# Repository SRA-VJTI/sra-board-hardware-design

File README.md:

<!-- PROJECT LOGO -->

[![Stargazers][stars-shield]][stars-url]
[![Forks][forks-shield]][forks-url]
[![Issues][issues-shield]][issues-url]
[![License][license-shield]][license-url]

<br/>

<p align="center">

  <h3 align="center">SRA Development Board</h3>
  <p align="center">
    ESP32-based Development Board
    <br />
    <a href="./sra_dev_board_2026">KiCAD</a>
    ·
    <a href="./gerber_sra_dev_board">Gerber</a>
    ·
    <a href="./documentation/images/board_images/front.png">Images</a>
    ·
    <a href="./3d_models/sra_board_model/sra_dev_board_2026.step">3D Model</a>
  </p>

# SRA Board 2026

The SRA board is a development board based on ESP32 with on-board peripherals like a programmable LED matrix, switches, sensor ports for Line Sensor Array and MPU-6050, protection circuit for over-current and reverse voltage, and motor drivers.

## Table of Contents

- [SRA Board 2026](#sra-board-2026)
  - [Table of Contents](#table-of-contents)
  - [Board Images](#board-images)
  - [About the Project](#about-the-project)
  - [Getting Started with a Development Board](#getting-started-with-a-development-board)
  - [Notable problems in the current SRA Board](#notable-problems-in-the-current-sra-board)
  - [Improvements Suggested for Future Iterations](#improvements-suggested-for-future-iterations)
  - [Potential Future Enhancements](#potential-future-enhancements)
  - [3D Models](#3d-models)
  - [Milestones](#milestones)
  - [Contributors](#contributors)
  - [Acknowledgements and Resources](#acknowledgements-and-resources)
  - [License](#license)

## Board Images

- **Frontside**

- **Backside**

## About the Project

- This development board is used for the [Wall-E](https://github.com/SRA-VJTI/Wall-E) and [MARIO](https://github.com/SRA-VJTI/MARIO) workshops conducted by [SRA](https://github.com/SRA-VJTI).
- Designed using KiCAD. The schematic and board files are [here](./sra_dev_board_2026).
- Resources for [previous work](https://github.com/SRA-VJTI/sra-board-hardware-design/tree/v2.5). For more details of the SRA board 2024, checkout this [link](https://github.com/SRA-VJTI/sra-board-hardware-design/releases/tag/v2.4).
- The SRA board 2023 images can be found [here](https://github.com/SRA-VJTI/sra-board-hardware-design/tree/v2.3/documentation/images).
- Older versions of the board and miscellaneous designs can be found [here](https://github.com/SRA-VJTI/PCB-Schematics-and-Layouts).

## Getting Started with a Development Board

In general, every development board has the following basic features:

- ### Power Supply Unit
  - Microcontrollers (MCUs) usually run on 3.3V or 5V logic supply voltage while input to a development board is normally 12V for motor and driving/controlling peripheral devices.
  - So, in order to have a single input source, a _power_ section which inter converts this 12V to standard levels like 5V & 3.3V for MCU and sensors is present.This is achieved using a step-down [buck regulator](https://www.youtube.com/watch?v=m8rK9gU30v4).
  - Buck Regulator IC [MP1584](./datasheets/MP1584_buck.pdf) is used in the current SRA Board 2026 for stepping down the voltage from 12V to 5V DC. This 5V is further regulated to 3.3V using LDO IC [AMS1117-3.3](./datasheets/ams1117_ldo.pdf). The MP1584 is a more compact and efficient alternative compared to the previous LM2576-S.
  - The previous edition of the SRA board (2025) used the [LM2576-S-5](./datasheets/lm2576_buck_regulator.pdf) buck regulator, while earlier editions used the LM7805 linear voltage regulator for stepping down from 12V to 5V.
  - The older editions of the SRA board used the LD33 linear voltage regulator for converting 5V to 3.3V at the sensor port.

- ### Motor Driver
  - Motors usually run on 12V and MCU output is generally 5V/3.3V. So, an external motor driver circuitry is required to control motors according to the MCU input.
  - The current and previous editions of SRA board use the [TB6612FNG](./datasheets/TB6612FNG_motor_driver.pdf) Motor Driver, which is a MOS-based H-Bridge motor driver.
  - The older editions of SRA Board used the L298N IC for motor-control, which is a BJT-based H-Bridge motor driver.

- ### Sensor Port
  - According to the external sensor types, usually development boards have onboard sensor ports where the sensors can be connected easily. [LSA - Line Sensor Array]() and [MPU- Motion Processing Unit]() have on-board connection ports.
  - The current edition uses easily available and efficient [JST XH connectors](https://en.wikipedia.org/wiki/JST_connector).
  - Previous versions used bulky [FRC connectors](<https://www.sunrom.com/c/frc-idc-flat-cable-box-header#:~:text=FRC%20(Flat%20Ribon%20Cable)%20are,from%206%20to%2064%20pins.>)

- ### Protection against [Reverse Voltage](https://www.google.com/url?sa=t&rct=j&q=&esrc=s&source=web&cd=&cad=rja&uact=8&ved=2ahUKEwjc8aaX1c3rAhXXXSsKHXphBgQQFjABegQICxAD&url=https%3A%2F%2Fwww.ti.com%2Flit%2Fpdf%2Fslva139&usg=AOvVaw0Qbub75JJ986MzLv6FYWKE)
  - The SRA Boards use diodes for reverse voltage protection in the power-line.
  - 12V Motor line and power regulated line have been separated with [SS34](./datasheets/ss34_3A_schottky_diode.pdf) and [SS54](./datasheets/ss24_2A_schottky_diode.pdf) schottky diodes respectively.

- ### Protection against [Over Current](https://www.baypower.com/blog/what-is-overcurrent-protection/#:~:text=Overcurrent%20protection%20is%20the%20method,of%20a%20piece%20of%20equipment.)
  - Earlier, for the overcurrent protection of MCU and motor driver circuit, bulky glass fuses of 300mA and 3A were used respectively. After breakdown, they used to be replaced.
  - In the recent versions of the board, these were replaced with compact, PTC Resettable Fuses.
  - On 12V line - [RXEF160](./datasheets/RUEF160_3,2A_trip_ptc_fuse.pdf) : 1.6A hold current; 3.2A trip current Fuse was used.
  - On 5V line - [RXEF160](./datasheets/RXEF050_1A_trip_ptc_fuse.pdf) : 0.5A hold current; 1A trip current Fuse was used.
- ### Programmable Switches and LEDs
  - Every development board should have some programmable switches and LEDs for testing, control and debugging purposes.
  - The current SRA Board 2026 features a 6x5 LED matrix (30 LEDs total) controlled via shift registers, which provides enhanced debugging capabilities and expressive visual feedback while reducing GPIO usage compared to discrete LEDs.
  - The previous edition (2025) had an array of 8 programmable discrete LEDs and switches.
  - The earlier editions had fewer programmable switches and LEDs for testing and control purposes.

- ### Power Switch
  - All versions have a power switch for the motor driver, using which power supply to the motor driver can be toggled. Similarly, there was a switch for the ESP32 MCU.

> Now that we covered basics of development boards, let us talk about the changes made in the new design.

## Changes IN SRA Board Over the years from 2024-2026

|            Feature            |           SRA Board 2024           |           SRA Board 2025           |            SRA Board 2026            |
| :---------------------------: | :--------------------------------: | :--------------------------------: | :----------------------------------: |
|           12V to 5V           |      LM2576-S Buck Converter       |      LM2576-S Buck Converter       |        MP1584 Buck Converter         |
|  Reverse Voltage Protection   |               Diodes               |               Diodes               |                Diodes                |
|   Line Sensing Arrays (LSA)   |             IR Sensors             |             IR Sensors             |              IR Sensors              |
|     Number of LSA Sensors     |                 5                  |                 5                  |                  5                   |
|         Motor Driver          |             TB6612FNG              |             TB6612FNG              |              TB6612FNG               |
|     Stepper Motor Driver      |                 -                  |                 -                  |                  -                   |
|   No. of DC Motor Channels    |                 2                  |                 2                  |                  2                   |
| No. of Stepper Motor Channels |                 0                  |                 0                  |                  0                   |
|        No. of Switches        |                 2                  |                 2                  |                  2                   |
|          No. of LEDs          |                 8                  |                 8                  | 6x5 LED Matrix (via Shift Registers) |
|    Over Current Protection    |        PTC Resettable Fuses        |        PTC Resettable Fuses        |         PTC Resettable Fuses         |
|    Sensor Port Connectors     |           JST Connectors           |           JST Connectors           |            JST Connectors            |
| Component Type and Board Size | SMD(Surface Mount Device), Smaller | SMD(Surface Mount Device), Smaller |  SMD(Surface Mount Device), Smaller  |
|         ESP32 Module          |           Not Integrated           |    Mounted and Soldered to PCB     |     Mounted and Soldered to PCB      |
|         Flashing Port         |             Micro USB              |               Type-C               |                Type-C                |

- ### **Compatiblity of SRA Board with Battery [3- 3.3V 2500mAh Batteries](https://robu.in/product/bak-nmc-18650-2500mah-8c-lithium-ion-battery/?gad_source=1&gclid=Cj0KCQjw6PGxBhCVARIsAIumnWb20iyJUEXE8V6eAfSambP35PfBsSFKje-ALjyNniqGYCW_kz3IbcQaAoeGEALw_wcB)**
  - The SRA Board is compatible with **3-cell (3S) Lithium-ion battery packs** which use an external **[BMS (Battery Management System)](https://robu.in/product/3s-10a-12v-18650-lithium-battery-charger-board-protection-module/)**.
  - The BMS helps maintain safe operating voltages and disconnects the battery when the voltage drops below a safe limit.
  - It also ensures balanced charging and discharging of the three cells, improving the overall health and lifetime of the battery pack.

- ### **7805 (5V linear regulator) to [LM2576/96 Buck Convertor](https://www.youtube.com/watch?v=m8rK9gU30v4)**
  - The higher efficiency, output current capability and reliability of LM2576/96 were the primary reasons for this change.
  - The efficiency of LM2576 can reach up to **~92%**, which is significantly better than the 7805 linear regulator.
  - The LM2576 can provide currents up to **3A**, allowing peripherals such as the MARIO workshop manipulator to be powered using the onboard regulator.

- ### **LD33 (3.3V) to [AMS1117](http://www.advanced-monolithic.com/pdf/ams1117.pdf)**:
  - Older editions used the **LD33 IC** to step down from 5V to 3.3V.
  - This was later replaced with the **AMS1117-3.3 LDO**, which is more compact and widely used for stable 3.3V regulation.
  - (_AMS1117 is also used on the ESP32-DevKitC V4 module._)

- ### **Reverse voltage protection: Diodes to P-MOSFET**
  - Diodes placed in series with the power line introduce voltage drop and power loss compared to a **P-MOSFET based protection circuit**.
  - Due to the higher current requirements of the motors, managing diode size and current rating became difficult.
  - Therefore, earlier versions used a **P-MOSFET based reverse polarity protection circuit**, which is more efficient and can handle higher currents.
  - In the current edition, **SMD Schottky diodes** are used, making size and rating less of an issue.

- ### **Component Type and Board Size**:
  - In the previous editions, THT/PTH (Through-Hole) components were used, which occupied more board area and increased in size with higher power ratings.
  - In the current edition, the design adopts a more compact SMD-based layout. The LM2576 buck converter has been replaced with the smaller MP1584 regulator, and the discrete LED array has been replaced with a 6×5 LED matrix driven using shift registers.
  - Current Board Dimensions: **90mm x 90mm**

- ### **L298N vs [TB6612FNG](https://dronebotworkshop.com/tb6612fng-h-bridge/)**
  - L298N is a BJT-based H-bridge motor driver but it is less efficient as compared to the new MOS-based TB6612FNG.
  - The detailed comparison is shown below. As you can see the efficiency of TB6612FNG can reach up to 91-95% which is significantly higher than the 40-70% efficiency of L298N.
  - The only drawback of TB6612FNG is the less continuous current which is equal to 1.2A.

- ### **LED System**

  - Earlier versions of the board used a set of discrete programmable LEDs for debugging and status indication. In the SRA Board 2026, this has been replaced with a **6×5 LED matrix driven using shift registers**.  
  - This significantly reduces GPIO usage while allowing more flexible visual debugging and status indication patterns.

## Notable problems in the current SRA Board

- ### **Buck Converter Stability Issue (MP1584)**
  - The SRA Board 2026 uses the **MP1584 buck converter** to step down 12V to 5V.
  - While the device allowed a significant reduction in the power section size compared to LM2576, irregular behaviour was observed under **higher load conditions**.
  - During heavy load scenarios involving motors and other peripherals, the **5V rail occasionally showed instability**, which may affect the overall system reliability.

- ### **USB Type-C Connector Mechanical Strength Issue**
  - The board currently uses a **16-pin USB Type-C connector** for programming and power.
  - In practical usage, the connector was found to be **mechanically weak**, and in some cases it could loosen or detach from the PCB after repeated cable insertion or mechanical stress.

- ### **Power Switch Issue**
  - There are two dpdt power toggle switch used on board. One to toggle the supply of 12v to the whole board and one to toggle the supply of 5v to the logic circuit.
  - Instead it should have been toggling 12v supply to the motors and toggling 12v supply to the whole board.

## Improvements Suggested for Future Iterations

Based on the current design of the SRA Board 2026, the following improvements are recommended for future iterations:

- **Replace MP1584 with TPS562202**: The TPS562202 offers improved reliability and enhanced long-term robustness compared to the current MP1584 buck converter. This component provides better thermal performance and more stable regulation across varying load conditions.

- **Upgrade to USB-C 6P Connector**: Replace the current Type-C connector with a robust USB-C 6P connector configuration. This simplifies soldering procedures, improves mechanical strength, and enhances durability during repeated connection cycles.

- **Add Unconnected UART Solder Pads (RX, TX)**: Incorporate unconnected solder pads for UART receive and transmit lines on the PCB. This allows the board to optionally function as a USB-to-TTL interface, extending its utility beyond standalone development applications.

## Potential Future Enhancements

The following experimental features and enhancements are being considered for future versions of the SRA Board but are not yet integrated into the 2026 iteration:

- **Onboard IMU Integration**: Direct integration of an Inertial Measurement Unit (IMU) for advanced motion sensing applications, eliminating the need for external MPU6050 connections.

- **Camera FFC/FPC Connector**: Addition of a Flat Flex Cable (FFC) or Flexible Printed Circuit (FPC) connector to support camera modules, enabling vision-based robotics projects and computer vision applications.

- **Integrated Motor Driver**: Direct onboarding of motor driver circuits instead of requiring external TB6612FNG modules, reducing component count and improving form factor.

- **CH340 to CP2102 Upgrade**: Replacing the CH340 USB-to-UART bridge with CP2102 for improved reliability, driver support across multiple operating systems, and better stability in industrial environments.

These enhancements represent opportunities for evolution of the platform and will be explored as future iterations of the board are developed.

## 3D Models

1. The complete 3D model (.step) file of [SRA Board 2026](./3d_models/sra_board_model/sra_dev_board_2026.step)
2. The 3D models of motor driver, LEDs, ESP32 etc.: [3d models of other components](./3d_models/)

<!-- Milestone -->

## Milestones

- [x] Designing of the prototype board
- [x] Modular testing of the circuit
- [x] Testing of prototype board
- [x] Final version
- [x] Making the board Battery Compatible
- [x] Onboard ESP32 Module

<!-- CONTRIBUTORS -->

## Contributors

- [Vishal Mutha](https://github.com/Vishal-Mutha): _Designer_
- [Atharva Atre](https://github.com/AtharvaAtre): _Mentor_
<!-- ACKNOWLEDGEMENTS AND REFERENCES -->

## Acknowledgements and Resources

- Previous Edition: [SRA Board 2025](https://github.com/SRA-VJTI/sra-board-hardware-design/releases/tag/v2.5)
- [KiCAD Tutorials](https://www.youtube.com/playlist?list=PL3bNyZYHcRSUhUXUt51W6nKvxx2ORvUQB)
- [README Template](https://github.com/roshanlam/ReadMeTemplate) by [roshanlam](https://github.com/roshanlam)

## License

- Distributed under the [MIT License](https://github.com/SRA-VJTI/sraboard-hardware-design/blob/master/LICENSE).

[forks-shield]: https://img.shields.io/github/forks/SRA-VJTI/sra-board-hardware-design
[forks-url]: https://github.com/SRA-VJTI/sra-board-hardware-design/network/members
[stars-shield]: https://img.shields.io/github/stars/SRA-VJTI/sra-board-hardware-design
[stars-url]: https://github.com/SRA-VJTI/sra-board-hardware-design/stargazers
[issues-shield]: https://img.shields.io/github/issues/SRA-VJTI/sra-board-hardware-design
[issues-url]: https://github.com/SRA-VJTI/sra-board-hardware-design/issues
[license-shield]: https://img.shields.io/github/license/SRA-VJTI/sra-board-hardware-design
[license-url]: https://github.com/SRA-VJTI/sra-board-hardware-design/blob/master/LICENSE

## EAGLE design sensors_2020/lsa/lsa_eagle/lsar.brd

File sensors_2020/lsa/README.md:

## LSA - Light Sensor Array

### Table of Contents
* [Overview](#overview)
* [Features](#features)
* [Components of LSA](#components-of-lsa)
* [Function of Components](#function-of-components)
	* [LED](#function-of-components)
	* [PhotoDiode](#function-of-components)
	* [IC LM324](#function-of-components)
	* [Resistors](#function-of-components)
* [Working Principle](#working-principle)
* [Appplications](#applications)
* [Scope of Improvement](#scope-of-improvement)
* [Description of Functions Used](#description-of-functions-used)

### Overview 
- The Light Sensor Array(LSA) is used to detect the white/black lined surface and it sends this data to the microcontroller ESP-32. Analyzing and processing the data received by the microcontroller ESP-32, the purpose of line following is achieved.

- Physical PCB

- PCB Model

###Features
* Components used are readily available.
* Easy connections for output signals.
* Compact enough to fit into any project.
* Distinguished trace widths for Signal and Power Routes.

### Components of LSA
| Component   | Description   | Quantity |
| ----------- | ------------- | -------- |
| LED         | Emits light   |  4       |
| PhotoDiode  | Absorbs light |  4       |
| IC LM324    | Op.Amp. IC    |  1       |  
| Resistors   | Limit Current |  8       |
|JST Connector | Connect PCB with other circuits|1|

### Function of Components
- LED
	- LSA consists of Four LED and PhotoDiode Pairs. The specific LED's emit white light which is incident on the surface and some of it is absorbed by the surface. The voltage source For the LEDs to glow is VCC.

- PhotoDiode
	- Based upon the reflectivity coefficient of the surface( generally less than 1), the remaining light reflected from the surface is captured by the Photodiodes. LEDs and complimentary photodiodes are used to efficiently detect the surface (white/black line) as the environment also contains unwanted light for the LSA sensor. The amount of light received is directly proportional to the current generated by it. More the light, more the current, more the reading.
 
- IC LM324 
	- This is a Quad(4) OP.Amp. IC. Op.Amp i.e Operation Amplifiers amplify the current with constant volatge. Since the current reading from photo diodes is significantly small and difficult to compare, it needs to be amplified. The 4 amplified outputs serve as raw readings of LSA.

- Resistors
	- Now to limit the current and thus to protect the LEDs, PhotoDiodes current limiting resistors are used.

### Working Principle
- LSA works on the principle of reflectivity of light for different types of surfaces.
	- Black Surface -> HIGH absorptivity -> LESS reflectivity
	- White Surface -> LOW absorptivity -> HIGH reflectivity
- Demonstration

### Applications
* Obstacle detection on a clear path.
* Line Following.
* Distinguish Colours on a path.

### Scope of Improvement
- LSA sometimes provides slightly inaccurate readings due to external light and conditions due to non uniformity of the colour of the path. Therefore, LSA has low accuracy. Hence LSA should be kept close to the ground.
- As of now only white and black surfaces are being mapped. Given accurate sensors and proper mapping we can map LSA for any range of RGB colours.

### Description of Functions Used
* ```c
    esp_err_t enable_line_sensor(int mode)	
    ```
    **Description** : Enables and Configures the adc(Analog to Digital Converter).	.

    **Parameters** :
    * `None` 

    **Returns** : esp_err_t returns ESP_OK if adc is initialised properly, else it returns ESP_ERR_INVALID_ARG
    
* ```c
    float bound(float val, float min, float max)	
    ```
    **Description** : Bounds the given val within the range [min, max].

    **Parameters** :
    * `val` : the value which needs to be bounded in the range [min, max].
    * `min` : the minimium limit value of the bounding range.
    * `max` : the maximum limit value of the bounding range.

    **Returns** : the bounded value of val within the bounding range.
    
* ```c
    float map(float val, float input_lower_limit, float input_higher_limit, float output_lower_limit, float output_higher_limit)	
    ```
    **Description** : Maps the range [input_lower_limit, input_higher_limit] to  the range [output_lower_limit, output_higher_limit].

    **Parameters** :
    * `val` : the value which needs to be mapped.
    * `input_lower_limit` : the minimium limit value of the input mapping range.
    * `input_lower_limit` : the maximum limit value of the input mapping range.
    * `output_lower_limit` : the minimium limit value of the output mapping range.
    * `output_lower_limit` : the maximum limit value of the output mapping range.
    
    **Returns** : the mapped value of val lying within the output mapping range.
    
* ```c 
    void vTaskDelay(const TickType_t xTicksToDelay)
  ```

  **Description** : Delay a task for a given number of ticks.The constant portTICK_PERIOD_MS can be used to calculate real time from the tick rate - with the     resolution of one tick period.

  **Parameters** : 
  * `xTicksToDelay` : The amount of time, in tick periods, that the calling task should block.

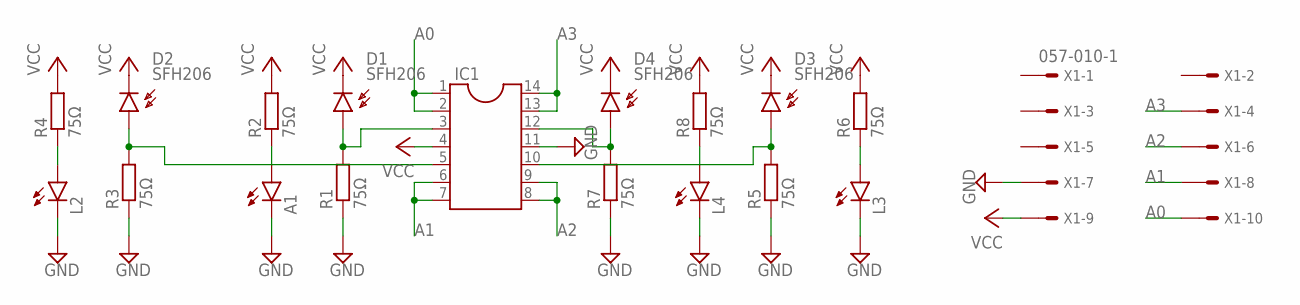
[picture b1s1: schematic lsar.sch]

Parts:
A1: LED3MM
D1, D2, D3, D4: SFH206
IC1: DIL14S; SOCKET-14
L2, L3, L4: LED3MM
R1, R2, R3, R4, R5, R6, R7, R8: 75Ω; 0207/10
X1: 057-010-1

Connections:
A0: IC1.1, IC1.2, X1.10
A1: IC1.6, IC1.7, X1.8
A2: IC1.8, IC1.9, X1.6
A3: IC1.13, IC1.14, X1.4
GND: A1.K (C), IC1.11, L2.K (C), L3.K (C), L4.K (C), R1.1, R3.1, R5.1, R7.1, X1.7
unnamed: A1.A, R2.1
unnamed: D1.A, IC1.3, R1.2
unnamed: L2.A, R4.1
unnamed: D2.A, IC1.5, R3.2
unnamed: L4.A, R8.1
unnamed: D4.A, IC1.12, R7.2
unnamed: L3.A, R6.1
NS7: D3.A, IC1.10, R5.2
VCC: D1.K (C), D2.K (C), D3.K (C), D4.K (C), IC1.4, R2.2, R4.2, R6.2, R8.2, X1.9

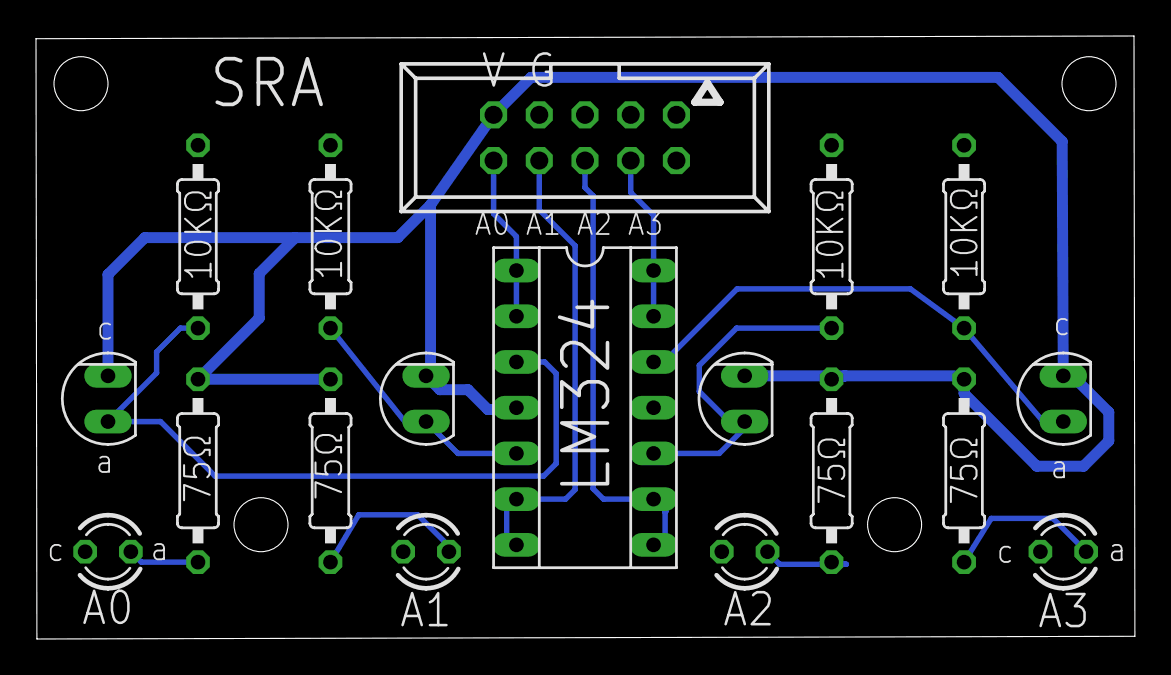
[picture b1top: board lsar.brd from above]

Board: 2 copper layers, 61.0 x 33.5 mm, 18 parts (0 on the bottom side), 14 nets.

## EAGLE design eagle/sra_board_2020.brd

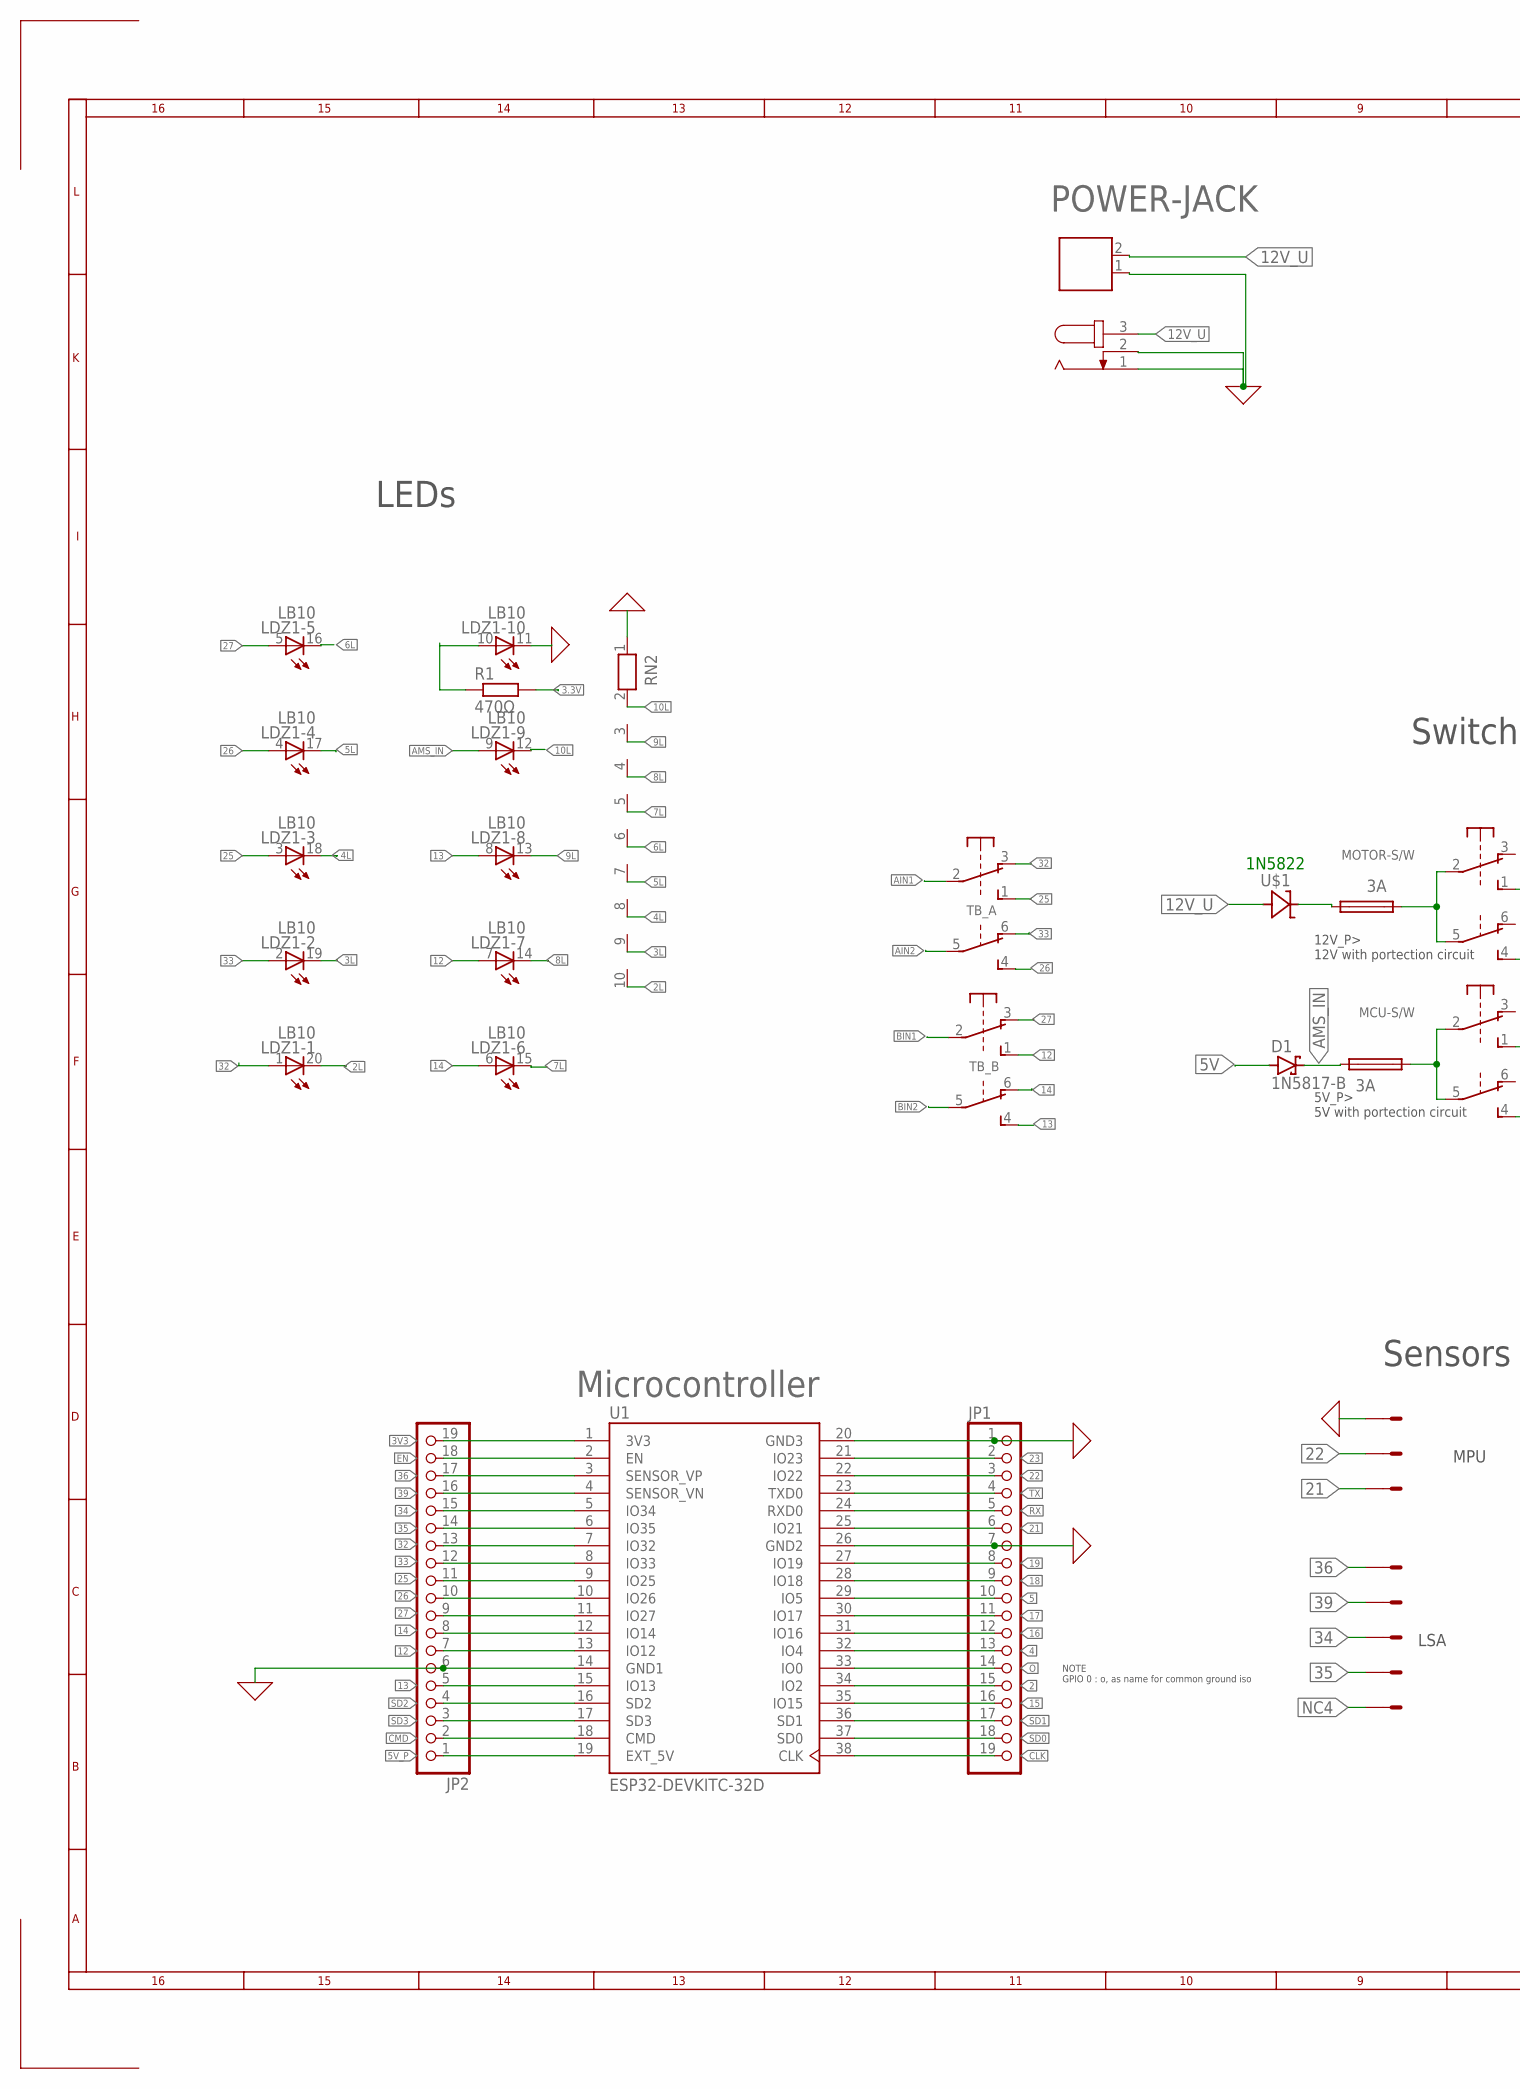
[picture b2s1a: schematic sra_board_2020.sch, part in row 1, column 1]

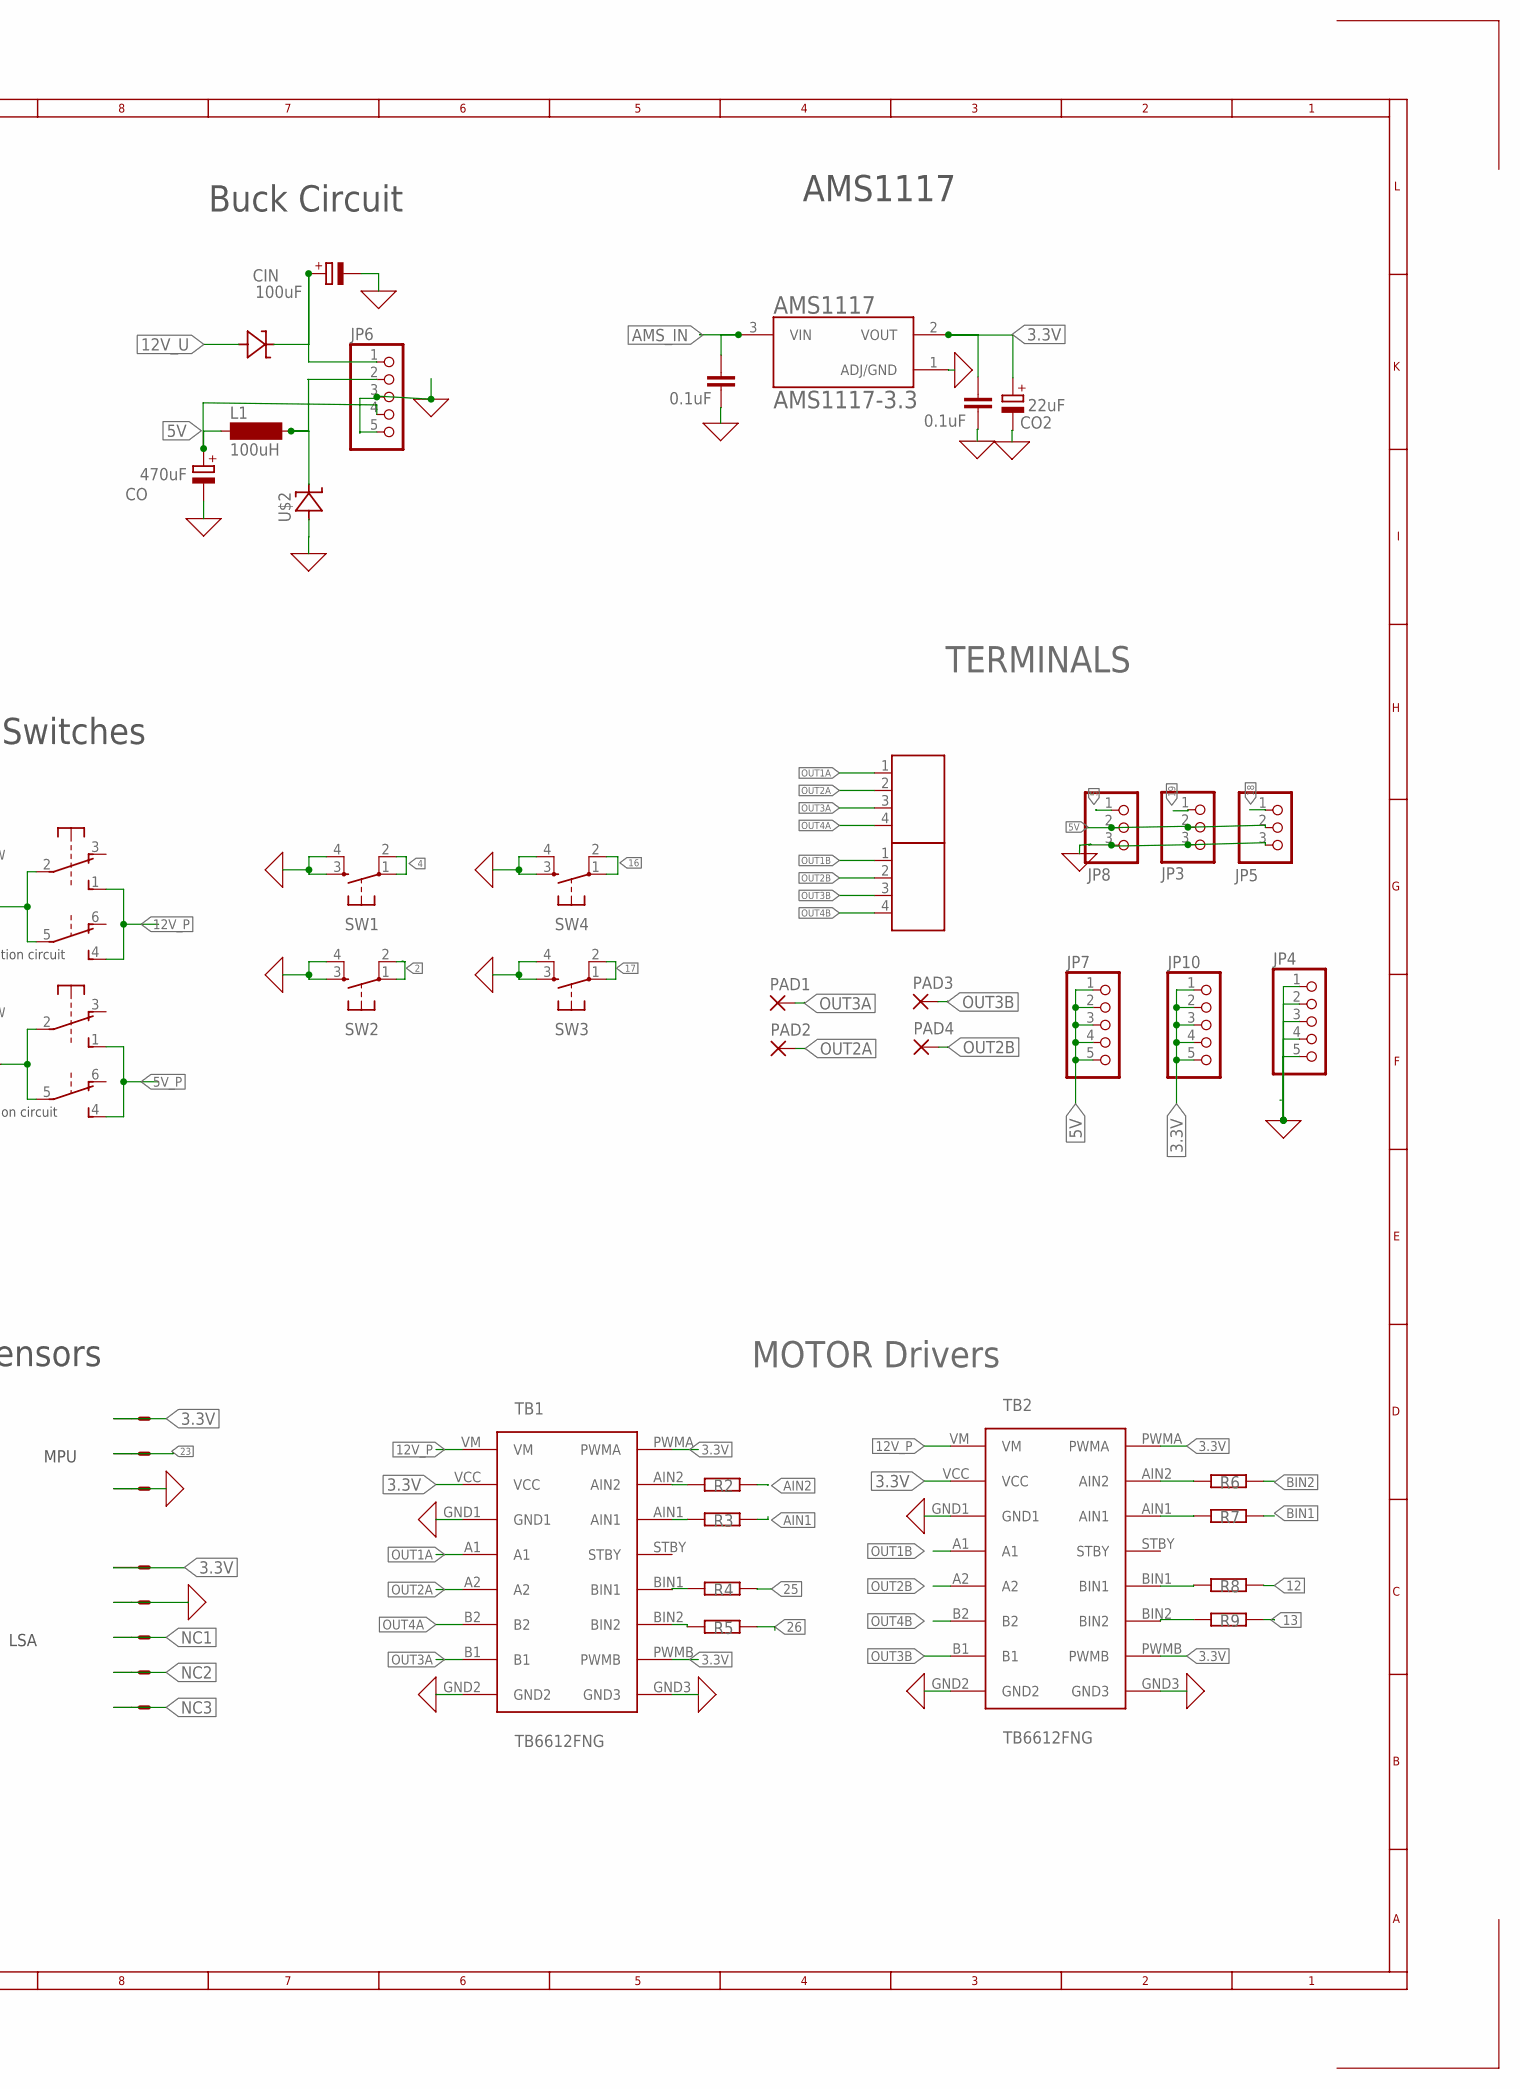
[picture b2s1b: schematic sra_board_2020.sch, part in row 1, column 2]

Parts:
12V: 691131710002
AMS1117: AMS1117-3.3; SOT229P700X180-4N
CIN: 100uF; E2,5-6
CIN1: 0.1uF; C5B2.5
CO: 470uF; E3,5-10
CO1: 0.1uF; C5B2.5
CO2: 22uF; E2,5-6
D1: 1N5817-B; DO41-7.6
F2, F3: 3A; SH25
J1, J2: 691131710004
JP1, JP2: PINHD-1X19; 1X19
JP3, JP5, JP8: PINHD-1X3; 1X03
JP4, JP6, JP7, JP10: PINHD-1X5; 1X05
L1: 100uH; SD12K100
LDZ1: LB10
LINE-SENSOR: 057-010-1
MCU-S/W: 9077-2
MOTOR-S/W: 9077-2
PAD1, PAD2, PAD3, PAD4: SMD2; SMD1,27-2,54
POWER-JACK: JACK-PLUG1; SPC4078
R1: 470Ω; 0204/7
R2, R3, R4, R5, R6, R7, R8, R9: 1KΩ; 0204/7
RN2: RN09; RN-10
SW1, SW2, SW3, SW4: DTS-6
TB1, TB2: TB6612FNG
TB_A: 9077-2
TB_B: 9077-2
U1: ESP32-DEVKITC-32D; MODULE_ESP32-DEVKITC-32D
U$1, U$2: 1N5399_SQUARE; C2673
U$3: 1N5399_ROUND; D-10
X1: 057-006-1

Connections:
0: 12V.1, AMS1117.1 (ADJ/GND), CIN.-, CIN1.1, CO.-, CO1.1, CO2.-, JP1.1, JP1.7, JP2.6, JP3.3, JP4.1, JP4.2, JP4.3, JP4.4, JP4.5, JP5.3, JP6.3, JP6.5, JP8.3, LDZ1.11 (C), LINE-SENSOR.4, POWER-JACK.1, POWER-JACK.2, RN2.1, SW1.3, SW1.4, SW2.3, SW2.4, SW3.3, SW3.4, SW4.3, SW4.4, TB1.GND1, TB1.GND2, TB1.GND3, TB2.GND1, TB2.GND2, TB2.GND3, U1.14 (GND1), U1.20 (GND3), U1.26 (GND2), U$2.A, X1.1, X1.6
2: JP1.15, SW2.1, SW2.2, U1.34 (IO2)
2L: LDZ1.20 (C), RN2.10
3.3V: AMS1117.2 (VOUT), CO1.2, CO2.+, JP10.1, JP10.2, JP10.3, JP10.4, JP10.5, LINE-SENSOR.2, R1.2, TB1.PWMA, TB1.PWMB, TB1.VCC, TB2.PWMA, TB2.PWMB, TB2.VCC, X1.2
3L: LDZ1.19 (C), RN2.9
3V3: JP2.19, U1.1 (3V3)
4: JP1.13, SW1.1, SW1.2, U1.32 (IO4)
4L: LDZ1.18 (C), RN2.8
5: JP1.10, JP8.1, U1.29 (IO5)
5L: LDZ1.17 (C), RN2.7
5V: CO.+, D1.A, JP3.2, JP5.2, JP6.4, JP7.1, JP7.2, JP7.3, JP7.4, JP7.5, JP8.2, L1.1
5V_P: JP2.1, MCU-S/W.1 (S), MCU-S/W.4 (S), U1.19 (EXT_5V)
5_AF: F2.1, MCU-S/W.2, MCU-S/W.5
6L: LDZ1.16 (C), RN2.6
7L: LDZ1.15 (C), RN2.5
8L: LDZ1.14 (C), RN2.4
9L: LDZ1.13 (C), RN2.3
10L: LDZ1.12 (C), RN2.2
12: JP2.7, LDZ1.7 (A), R8.2, TB_B.1 (S), U1.13 (IO12)
12V_AF: F3.2, MOTOR-S/W.2, MOTOR-S/W.5
12V_P: MOTOR-S/W.1 (S), MOTOR-S/W.4 (S), TB1.VM, TB2.VM
12V_U: 12V.2, POWER-JACK.3, U$1.A, U$3.A
13: JP2.5, LDZ1.8 (A), R9.2, TB_B.4 (S), U1.15 (IO13)
14: JP2.8, LDZ1.6 (A), TB_B.6 (O), U1.12 (IO14)
15: JP1.16, U1.35 (IO15)
16: JP1.12, SW4.1, SW4.2, U1.31 (IO16)
17: JP1.11, SW3.1, SW3.2, U1.30 (IO17)
18: JP1.9, JP5.1, U1.28 (IO18)
19: JP1.8, JP3.1, U1.27 (IO19)
21: JP1.6, U1.25 (IO21), X1.5
22: JP1.3, U1.22 (IO22), X1.3
23: JP1.2, U1.21 (IO23), X1.4
25: JP2.11, LDZ1.3 (A), R4.2, TB_A.1 (S), U1.9 (IO25)
26: JP2.10, LDZ1.4 (A), R5.2, TB_A.4 (S), U1.10 (IO26)
27: JP2.9, LDZ1.5 (A), TB_B.3 (O), U1.11 (IO27)
32: JP2.13, LDZ1.1 (A), TB_A.3 (O), U1.7 (IO32)
33: JP2.12, LDZ1.2 (A), TB_A.6 (O), U1.8 (IO33)
34: JP2.15, LINE-SENSOR.5, U1.5 (IO34)
35: JP2.14, LINE-SENSOR.7, U1.6 (IO35)
36: JP2.17, LINE-SENSOR.1, U1.3 (SENSOR_VP)
39: JP2.16, LINE-SENSOR.3, U1.4 (SENSOR_VN)
AIN1: R3.2, TB_A.2
AIN2: R2.2, TB_A.5
AMS_IN: AMS1117.3 (VIN), CIN1.2, D1.C, F2.2, LDZ1.9 (A)
BIN1: R7.2, TB_B.2
BIN2: R6.2, TB_B.5
CLK: JP1.19, U1.38 (CLK)
CMD: JP2.2, U1.18 (CMD)
EN: JP2.18, U1.2 (EN)
unnamed: LDZ1.10 (A), R1.1
unnamed: R2.1, TB1.AIN2
unnamed: R3.1, TB1.AIN1
unnamed: R4.1, TB1.BIN1
unnamed: R5.1, TB1.BIN2
unnamed: R6.1, TB2.AIN2
unnamed: R7.1, TB2.AIN1
unnamed: R8.1, TB2.BIN1
unnamed: R9.1, TB2.BIN2
unnamed: JP6.2, L1.2, U$2.C
unnamed: F3.1, U$1.C
unnamed: CIN.+, JP6.1, U$3.C
NC1: LINE-SENSOR.6
NC2: LINE-SENSOR.8
NC3: LINE-SENSOR.10
NC4: LINE-SENSOR.9
O: JP1.14, U1.33 (IO0)
OUT1A: J1.1, TB1.A1
OUT1B: J2.1, TB2.A1
OUT2A: J1.2, PAD2.1, TB1.A2
OUT2B: J2.2, PAD4.1, TB2.A2
OUT3A: J1.3, PAD1.1, TB1.B1
OUT3B: J2.3, PAD3.1, TB2.B1
OUT4A: J1.4, TB1.B2
OUT4B: J2.4, TB2.B2
RX: JP1.5, U1.24 (RXD0)
SD0: JP1.18, U1.37 (SD0)
SD1: JP1.17, U1.36 (SD1)
SD2: JP2.4, U1.16 (SD2)
SD3: JP2.3, U1.17 (SD3)
TX: JP1.4, U1.23 (TXD0)

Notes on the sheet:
TERMINALS
MOTOR Drivers
Microcontroller
Buck Circuit
Switches
12V_P> 12V with portection circuit
5V_P> 5V with portection circuit
Sensors
MPU
LSA
NOTE GPIO 0 : o, as name for common ground iso
AMS1117
LEDs
1N5822

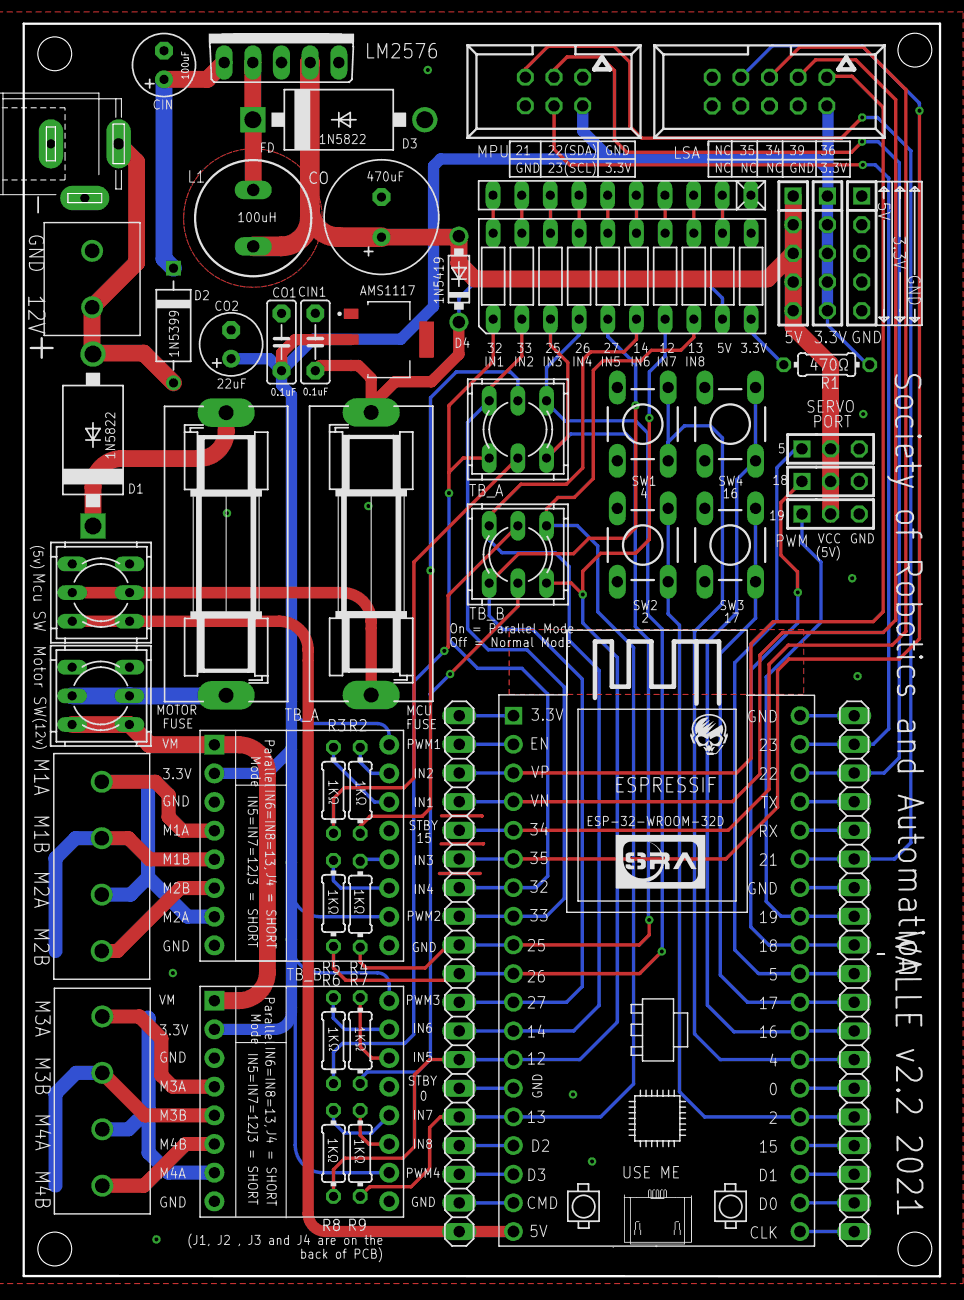
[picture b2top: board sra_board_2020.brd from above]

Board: 2 copper layers, 81.2 x 111.0 mm, 54 parts (0 on the bottom side), 76 nets.

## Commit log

2020-09-04 README and Eagle files added
2020-09-04 External Eagle libraries added
2020-09-04 READE updated
2020-09-05 Gerber added and README updated
2020-09-05 README updated
2020-09-05 LOGO changed
2020-09-05 minor update
2020-09-05 Extra folder deleted
2020-09-05 Foldername changed
2020-09-05 foldername and filename changed
2020-09-05 foldername changed and README updated
2020-09-07 filename renamed
2020-09-07 Directory restructured, updated README
2020-09-09 minor fix in readme
2020-09-17 Datasheets Added
2020-09-17 ESP32 Hardware guideline Added
2021-01-10 Renamed Eagle files and Added Series Resistor Between ESP and Motor Driver
2021-01-10 OSH park tag added in README
2021-01-11 Change the placement of Series Resistors and cleaned the routing
2021-01-16 Mosfet Replaced by two individual Diodes
2021-01-23 Front and back silkscreen improved
2021-01-23 Added New Footprints
2021-01-23 Added Images of Final Board
2021-01-23 Gerber File added and readme updated
2022-01-08 Sensor eagle and kicad files added
2022-01-08 lsa files cleaned
2022-01-23 Imported SRA 2020 board eagle -> Kicad6, organised structure, footprint libs
2022-01-23 Updated year in README.md
2022-01-23 SRA Board 2022: Porting to Kicad 6.0 (#4)
    * Imported SRA 2020 board eagle -> Kicad6, organised structure, footprint libs
    * Updated year in README.md
2022-01-23 Corrected Schematics for KiCad 6
2022-01-30 Added project files for fresh 2022 SRA Dev Board
2022-01-31 Finalised SRA Dev Board 2022 Design, added gerbers, renders, assets
2022-01-31 Updated gerbers, board image assets
2022-01-31 Fixed names and images in sra_board_images.md
2022-01-31 Added Interactive BOM, SMT pick place files
2022-02-01 fixed untracked files
2022-02-01 Added PCB files for LSA and MPU 2022
2022-02-01 First prototype gerber files added, fixed project structure, kicad files
2022-02-06 Created a README for MPU 6050
2022-02-07 Merged the Wall-E and my README
2022-02-08 Updated SRA-board images, updated the 3d view image in assets fiolder under documentation folder & added LSA and MPU folder under documentationn/images
2022-02-08 updated the sra_board_images.md file
2022-02-08 LSA Readme added.
2022-02-08 LSA Readme updated.
2022-02-08 Minor changes made
2022-02-08 ESP Functions removed
2022-02-08 Connection edited
2022-02-08 Connection of MPU6050 with SRA Board
    Added image of MPU6050 connection with SRA Board
2022-02-08 images dimensions changed.
2022-02-08 readme name changed
2022-02-08 Renamed MPU readme file
2022-02-09 Added cad, step and .wrl files for lsa, mpu and sra_board under 3d_model folder
2022-02-09 Removed the other_components_model folder under 3d_models And renamed the sra_board_images.md to README.md
2022-02-10 SRA Board 2022 Doc
2022-02-10 3d-view of 2022 Board
2022-02-10 Image for FRC Connectors
2022-02-10 Image for JST-PH COnnectors
2022-02-10 2022 SRA board Doc
2022-02-10 Deleted jpeg file
2022-02-10 Image for JST PH Connectors
2022-02-13 Images aligned to center and Readme name changed.
2022-02-13 Image and gif dimensions changed.
2022-02-13 2022 Updated Doc
2022-02-14 Asset folder in lsa removed and moved the content to documentation.
2022-02-14 Sources of images and gif changed in README
2022-02-19 Documentation for SRA Board 2022
2022-02-22 Testing documentation website
2022-03-06 SRA Board, MPU, LSA Kicad, Gerber files updated
2022-08-28 Update README.md Add renders, datasheets, documentation
2022-11-01 Fixed readme errors
2022-11-03 add DRV8825 Stepper Driver
2022-11-10 Add footprint and symbol for DRV8825 and update schematic
2022-11-10 Modify routing according to new schematic
2022-11-10 modify silkscreen
2022-11-11 add TCRT-5000 base structure to LSA
2022-11-13 Update PCBs for Wall-E 2023
    Additions:
    1. Add new LSA
    2. Add new fabrication outputs for SRA board and LSA.
    3. Add terminal block for ground connection for shielding.
    Modifications:
    1. Modify MCU switch placement.
2022-11-20 Updated gerbers for LSA and SRA-Board
2022-11-22 Updated working content for sra_dev_board_2023
2022-11-22 updated BoM for sra_board_2023
2022-11-22 Add 3D model for TCRT5000
2022-11-22 Tweaks in routing prototype-1
2022-11-23 Add updated 3d renders for sra-dev-board-2023
2022-12-10 Resolve LSA wiring problem and fixed silkscreen, updated gerbers, fabrication outputs and 3D files for LSA
2022-12-15 Update LSA and SRA board after hardware testing
2023-01-09 Update repo with recent changes
2023-01-11 Modify relative path for TCRT5000 footprint
2023-01-13 added
2023-01-19 Motor Driver images changed
2023-01-26 added pinout diagrams for mpu,lsa and sra boards
2023-01-27 changed README to include pinout images and made changes to README with latest changes
2023-01-27 fixed README to show images
2023-02-02 removed unnecessary files
2023-02-21 Add current limiting resistor on Interrupt line for MPU
2023-02-21 Update gerbers, placement files and BoM
2023-03-26 Minor changes to README for new SRA BOARD, added new images
2023-03-26 minor changes
2023-03-30 Updates to README for SRA BOARD 2023 (#25)
    * added pinout diagrams for mpu,lsa and sra boards
    * changed README to include pinout images and made changes to README with latest changes
    * fixed README to show images
    * Minor changes to README for new SRA BOARD, added new images
    * minor changes
2023-03-30 Add current limiting resistor for MPU (#26)
    * Add current limiting resistor on Interrupt line for MPU
    * Update gerbers, placement files and BoM
2024-05-10 SRA Board 2023-24 Updated
2024-05-10 Readme SRA Board Updated
2024-05-10 Parallel Mode Removed
2024-05-14 SRA Board 23-24 Updated
2025-04-10 Fixes: addressed PR review comments
2025-06-25 Revert "Updated Readme and assets for SRA board 2024-25"
2025-06-25 Update the assets and readme as per SRA Board 2024-25 (#33)
2026-03-06 SRA Board 2025-26 Update
2026-03-07 readme update for 2025-26 SRA Board
2026-03-14 Update for the SRA Board 2025-26 (#34)
    * SRA Board 2025-26 Update
    * readme update for 2025-26 SRA Board

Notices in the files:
README.md:
License:
- Distributed under the [MIT License](https://github.com/SRA-VJTI/sraboard-hardware-design/blob/master/LICENSE).
parts and their libraries:
Wurth_Elektronik_Electromechanic_Termina: Copyright: Würth Elektronik
